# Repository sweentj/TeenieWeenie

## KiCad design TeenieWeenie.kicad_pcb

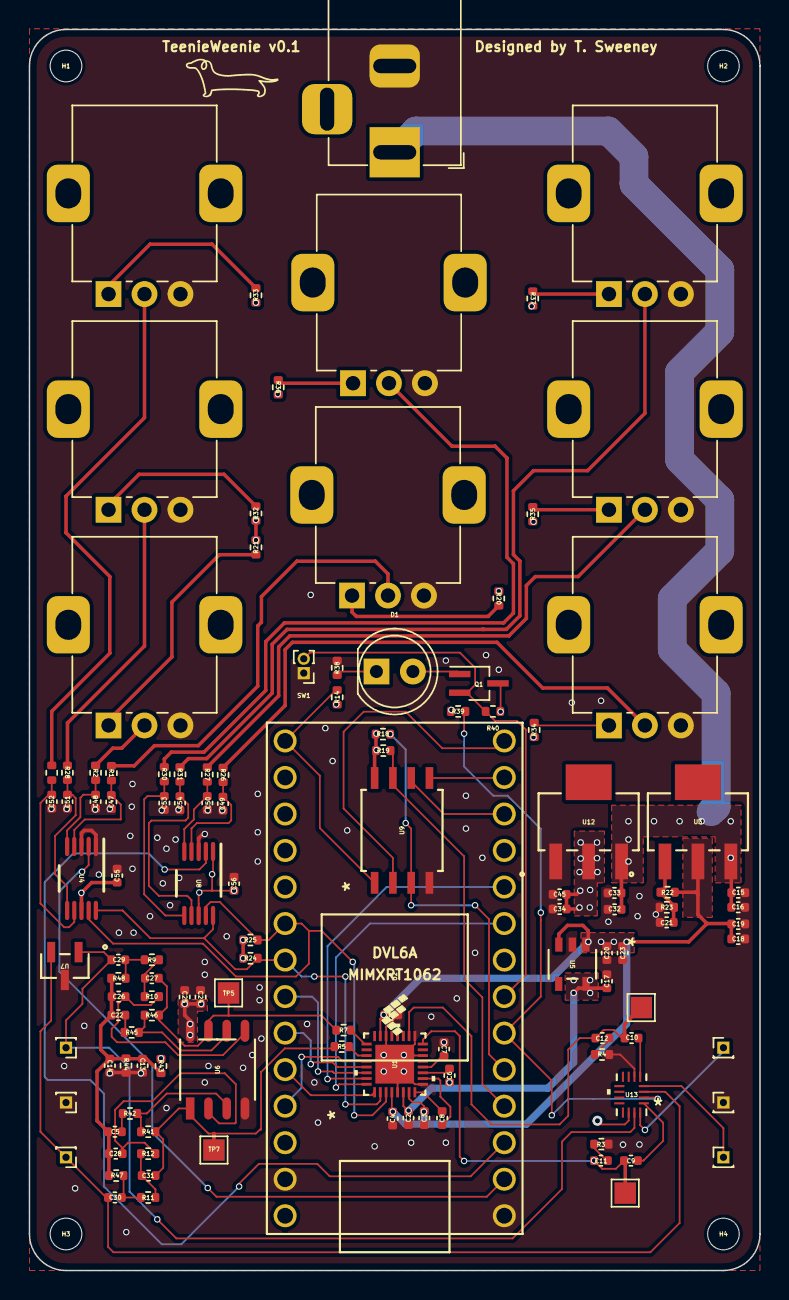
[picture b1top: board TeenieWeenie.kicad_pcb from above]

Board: 4 copper layers, 50.8 x 86.3 mm, 124 parts (0 on the bottom side), 79 nets.

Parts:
C1, C2, C11, C12: 0.1uF; C_0402_1005Metric
C3, C4: 4.7uF; C_0402_1005Metric
C5, C13, C17, C22: 1u; C_0402_1005Metric
C6, C7, C8: 2.2uF; C_0402_1005Metric
C9, C10, C29, C30: 4.7u; C_0402_1005Metric
C14: 100n; C_0402_1005Metric
C15, C21, C23, C25, C32: 10u; C_0402_1005Metric
C16, C19, C20, C24, C33, C45, C55, C56: 0.1u; C_0402_1005Metric
C18, C34: 22u; C_0402_1005Metric
C26, C28: 10p; C_0402_1005Metric
C27, C31: 100p; C_0402_1005Metric
C47, C48, C49, C50, C51, C52, C53, C54: 160p; C_0402_1005Metric
D1: LED; LED_D5.0mm
H1, H2, H3, H4: MountingHole; MountingHole_2.2mm_M2_DIN965
J1: Barrel_Jack; BarrelJack_Horizontal
J2, J3, J4, J5, J6, J8: Conn_01x01; PinHeader_1x01_P1.00mm_Vertical
Q1: DMP2160UW-7; SOT-323_SC-70_Handsoldering
R1, R2, R26, R27, R28, R29, R30, R31: 2k; R_0402_1005Metric
R3, R4: 20; R_0402_1005Metric
R5, R7: 0; R_0402_1005Metric
R9, R11, R38: 1k; R_0402_1005Metric
R10, R12: 31.1k; R_0402_1005Metric
R14, R18, R19, R20, R21, R24, R25, R32, R33, R34, R35, R36, R37, R39: 5k; R_0402_1005Metric
R22: 33k; R_0402_1005Metric
R23: 15k; R_0402_1005Metric
R40, R41, R42, R43, R44, R45, R46: 10k; R_0402_1005Metric
R47, R48: 1M; R_0402_1005Metric
RV1, RV2, RV3, RV4, RV5, RV6, RV7, RV8: R_Potentiometer; POT_PTV09A-4025U-B104
SW1: SW_Push; PinHeader_1x02_P1.00mm_Vertical
TP5, TP7, TP17, TP18: TestPoint; TestPoint_Pad_1.5x1.5mm
U1: WM8904CGEFL/V; QFN32_4X4_CIR
U2: Teensy4.0; Teensy40_1
U3: AMS1117-ADJ; SOT_AMS_ADS
U4, U8: ADS1015IDGSR; DGS0010A_N
U5: TLV74010PDQNR; SOT_PDQNR_TEX
U6: AP358SG-13; SOP-8L_DIO
U7: SM05T1G; SOT-23_ONS
U9: W25Q128JVSIQ TR; SOIC_208MIL_WIN
U12: AMS1117-3.3; SOT_AMS_ADS
U13: FSA2466UMX; UMLP16_1P8X2P6_ONS

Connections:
+1V0: C2.1, C6.2, C17.1, U1.6 (DCVDD), U5.5 (OUT)
+1V8: C1.1, C3.1, C4.1, C18.1, C19.1, C20.1, C23.1, R22.1, U1.4 (DBVDD), U1.7 (CPVDD), U1.23 (AVDD), U3.2 (VOUT), U5.1 (IN), U5.3 (EN)
+3V3: C24.1, C25.1, C34.1, C45.1, C55.1, C56.1, Q1.3 (S), R14.1, R18.1, R19.1, R20.2, R21.2, R24.1, R25.1, R32.2, R33.2, R34.2, R35.2, R36.2, R37.2, R39.1, R40.1, R43.2, U2.31 (3V3), U4.8 (VDD), U6.8 (V+), U8.1 (ADDR), U8.8 (VDD), U9.8 (VCC), U12.2 (VOUT), U13.14 (VCC)
/ADC/AIN0_0: C47.1, R1.2, U4.4 (AIN0)
/ADC/AIN0_1: C49.1, R26.2, U8.4 (AIN0)
/ADC/AIN1_0: C48.1, R2.2, U4.5 (AIN1)
/ADC/AIN1_1: C50.1, R27.2, U8.5 (AIN1)
/ADC/AIN2_0: C51.1, R28.2, U4.6 (AIN2)
/ADC/AIN2_1: C53.1, R30.2, U8.6 (AIN2)
/ADC/AIN3_0: C52.1, R29.2, U4.7 (AIN3)
/ADC/AIN3_1: C54.1, R31.2, U8.7 (AIN3)
/ADC/POT1: R1.1, RV1.2
/ADC/POT2: R2.1, RV2.2
/ADC/POT3: R28.1, RV3.2
/ADC/POT4: R29.1, RV4.2
/ADC/POT5: R26.1, RV5.2
/ADC/POT6: R27.1, RV6.2
/ADC/POT7: R30.1, RV7.2
/ADC/POT8: R31.1, RV8.2
/ADC/SCL: R24.2, U1.2 (SCLK), U2.26 (19_A5_SCL0), U4.10 (SCL), U8.10 (SCL)
/ADC/SDA: R25.2, U1.3 (SDA), U2.25 (18_A4_SDA0), U4.9 (SDA), U8.9 (SDA)
/AFE/AudioL_Raw: C29.1, J2.1, U7.1 (CATHODE), U13.15 (1B1)
/AFE/AudioR_Raw: C30.1, J3.1, U7.2 (CATHODE), U13.3 (2B1)
/AFE/IN1+A: C28.1, R12.2, U6.2 (INVERTINGINPUT1)
/AFE/IN1-A: R41.1, R42.2, U6.3 (NON-INVERTINGINPUT1)
/AFE/IN2+A: C26.1, R10.2, U6.5 (NON-INVERTINGINPUT2)
/AFE/IN2-A: R45.2, R46.1, U6.6 (INVERTINGINPUT2)
/AFE/OUT1A: C31.2, R5.2, R41.2, TP7.1, U6.1 (OUTPUT1)
/AFE/OUT2A: C27.2, R7.2, R46.2, TP5.1, U6.7 (OUTPUT2)
/AudioCodec/AudioL_Dirty: C9.2, U13.1 (1B0)
/AudioCodec/AudioR_Dirty: C10.2, U13.5 (2B0)
/AudioCodec/LINEOUTL: C9.1, C11.1, TP17.1, U1.16 (LINEOUTL)
/AudioCodec/LINEOUTR: C10.1, C12.1, TP18.1, U1.18 (LINEOUTR)
/IOSwitch/AudioOut_L: J5.1, U13.16 (1A)
/IOSwitch/AudioOut_R: J6.1, U13.4 (2A)
/MCU/ADCDAT: U1.31 (ADCDAT), U2.10 (8_TX2_IN1)
/MCU/BCLK: U1.29 (BCLK/GPIO4), U2.28 (21_A7_RX5_BCLK1)
/MCU/CODC_IRQ: U1.1 (IRQ/GPIO1), U2.29 (22_A8_CTX1)
/MCU/DACDAT: U1.32 (DACDAT), U2.9 (7_RX2_OUT1A)
/MCU/LRCLK: U1.30 (LRCLK), U2.27 (20_A6_TX5_LRCLK1)
/MCU/MCLK: U1.28 (MCLK), U2.30 (23_A9_CRX1_MCLK1)
/MCU/~ADC_IRQ0: U2.2 (0_RX1_CRX2_CS1), U4.2 (ALERT_RDY)
/MCU/~ADC_IRQ1: U2.3 (1_TX1_CTX2_MISO1), U8.2 (ALERT_RDY)
/MCU/~BTN: Q1.2 (G), R40.2, SW1.2, U2.7 (5_IN2)
/MCU/~SWCTRL: R39.2, U2.6 (4_BCLK2), U13.2 (1S)
GND: C1.2, C2.2, C3.2, C4.2, C7.2, C13.2, C14.2, C15.2, C16.2, C17.2, C18.2, C19.2, C20.2, C21.2, C23.2, C24.2, C25.2, C32.2, C33.2, C34.2, C45.2, C47.2, C48.2, C49.2, C50.2, C51.2, C52.2, C53.2, C54.2, C55.2, C56.2, J1.2, J4.1, J8.1, R3.2, R4.2, R23.2, R38.2, R44.1, RV1.3, RV2.3, RV3.3, RV4.3, RV5.3, RV6.3, RV7.3, RV8.3, SW1.1, U1.5 (DGND), U1.9 (CPGND), U1.14 (HPOUTFB), U1.17 (LINEOUTFB), U1.22 (AGND), U1.33 (EPAD), U2.1 (GND), U2.32 (GND), U4.1 (ADDR), U4.3 (GND), U5.2 (GND), U6.4 (GND), U7.3 (ANODE), U8.3 (GND), U9.4 (GND), U12.1 (GROUND/ADJUST), U13.6 (GND)
unnamed: C5.2, R42.1
unnamed: C11.2, R3.1
unnamed: C12.2, R4.1
unnamed: C22.2, R45.1
unnamed: C27.1, R9.2, R10.1
unnamed: C29.2, R9.1, R48.2
unnamed: C30.2, R11.1, R47.2
unnamed: C31.1, R11.2, R12.1
unnamed: D1.2 (A), Q1.1 (D)
unnamed: D1.1 (K), R38.1
unnamed: R20.1, RV1.1
unnamed: R21.1, RV2.1
unnamed: R32.1, RV3.1
unnamed: R33.1, RV4.1
unnamed: R34.1, RV5.1
unnamed: R35.1, RV6.1
unnamed: R36.1, RV7.1
unnamed: R37.1, RV8.1
unnamed: C8.2, U1.8 (CPCA)
unnamed: C8.1, U1.10 (CPCB)
unnamed: C7.1, U1.12 (CPVOUTN)
unnamed: C6.1, U1.11 (CPVOUTP)
unnamed: R5.1, U1.27 (IN1L/DMICDAT1)
unnamed: R7.1, U1.25 (IN1R/DMICDAT2)
unnamed: R19.2, U2.4 (2_OUT2), U9.7 (/HOLD_/RESET)
unnamed: R18.2, U2.5 (3_LRCLK2), U9.3 (/WP(IO2))
unnamed: U2.12 (10_CS_MQSR), U9.6 (CLK)
unnamed: U2.13 (11_MOSI_CTX1), U9.5 (DI(IO0))
unnamed: U2.14 (12_MISO_MQSL), U9.2 (DO(IO1))
unnamed: R14.2, U2.20 (13_SCK_CRX1_LED), U9.1 (/CS)
unnamed: C21.1, R22.2, R23.1, U3.1 (GROUND/ADJUST)
VDD: C15.1, C16.1, C32.1, C33.1, J1.1, U3.3 (VIN), U12.3 (VIN)
Vdd2: C5.1, C13.1, C14.1, C22.1, C26.2, C28.2, R43.1, R44.2, R47.1, R48.1

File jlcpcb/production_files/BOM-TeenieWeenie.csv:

Comment,Designator,Footprint,LCSC
15k,R23,R_0402_1005Metric,C102812
5k,"R14,R18,R19,R20,R21,R24,R25,R32,R33,R34,R35,R36,R37,R39",R_0402_1005Metric,C105873
AMS1117-3.3,U12,SOT_AMS_ADS,C110474
SM05T1G,U7,SOT-23_ONS,C111172
1k,"R11,R38,R9",R_0402_1005Metric,C11702
AP358SG-13,U6,SOP-8L_DIO,C128760
10u,"C15,C21,C23,C25,C32",C_0402_1005Metric,C15525
ADS1015IDGSR,"U4,U8",DGS0010A_N,C193969
0.1uF,"C1,C11,C12,C16,C19,C2,C20,C24,C33,C45,C55,C56",C_0402_1005Metric,C2167244
20,"R3,R4",R_0402_1005Metric,C25089
33k,R22,R_0402_1005Metric,C25779
1M,"R47,R48",R_0402_1005Metric,C26083
TLV74010PDQNR,U5,SOT_PDQNR_TEX,C2995549
WM8904CGEFL/V,U1,QFN32_4X4_CIR,C323845
100p,"C27,C31",C_0402_1005Metric,C327198
160p,"C47,C48,C49,C50,C51,C52,C53,C54",C_0402_1005Metric,C363530
22u,"C18,C34",C_0402_1005Metric,C415703
FSA2466UMX,U13,UMLP16_1P8X2P6_ONS,C457657
100n,C14,C_0402_1005Metric,C541464
0,"R5,R7",R_0402_1005Metric,C60485
2k,"R1,R2,R26,R27,R28,R29,R30,R31",R_0402_1005Metric,C60488
10k,"R40,R41,R42,R43,R44,R45,R46",R_0402_1005Metric,C60490
AMS1117-ADJ,U3,SOT_AMS_ADS,C6188
10p,"C26,C28",C_0402_1005Metric,C76946
2.2uF,"C6,C7,C8",C_0402_1005Metric,C77002
4.7u,"C10,C29,C3,C30,C4,C9",C_0402_1005Metric,C82453
1u,"C13,C17,C22,C5",C_0402_1005Metric,C88945
W25Q128JVSIQ TR,U9,SOIC_208MIL_WIN,C97521
DMP2160UW-7,Q1,SOT-323_SC-70_Handsoldering,C99272

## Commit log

2023-10-28 Finalized schematic
2023-10-28 Added pots to schem
2023-10-31 final final schematic:
2023-11-02 rev1 of pcb component placement
2023-11-05 routed power
2023-11-18 redesign layout
2023-11-23 routing mostly complete
2023-12-31 final manufacturing files
